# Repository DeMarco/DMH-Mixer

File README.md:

# DMH-Mixer
Simple OpAmp based Mixer module

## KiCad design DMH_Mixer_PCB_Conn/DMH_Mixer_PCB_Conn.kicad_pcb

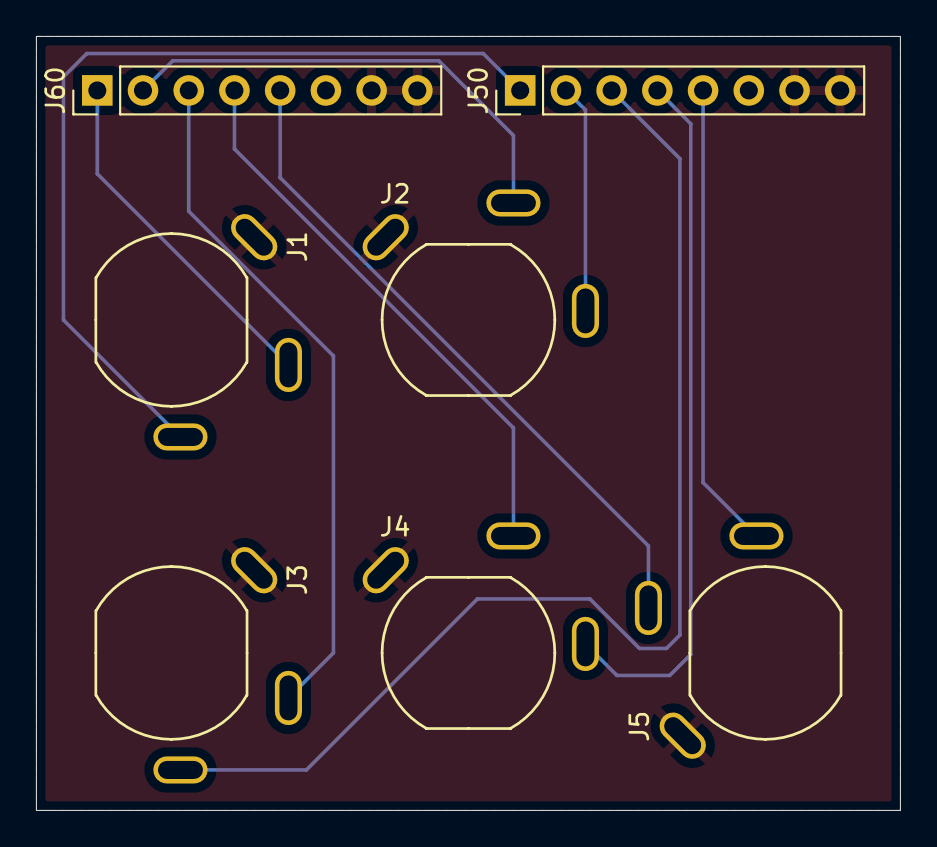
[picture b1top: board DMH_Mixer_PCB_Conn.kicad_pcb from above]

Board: 2 copper layers, 48.0 x 43.0 mm, 7 parts (0 on the bottom side), 11 nets.

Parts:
J1, J2, J3, J4, J5: TS_Jack_6.35mm_Sw; CUI_MJ-63052A
J50, J60: Conn_01x08; PinHeader_1x08_P2.54mm_Vertical

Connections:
/Inputs and Outputs/Input 1 Jack: J1.T, J50.1
/Inputs and Outputs/Input 2 Jack: J2.T, J50.2
/Inputs and Outputs/Input 3 Jack: J3.T, J50.3
/Inputs and Outputs/Input 4 Jack: J4.T, J50.4
/Inputs and Outputs/Output Jack: J5.T, J50.5
GND: J1.S, J2.S, J3.S, J4.S, J5.S, J50.7, J50.8, J60.7, J60.8
unnamed: J1.TN, J60.1
unnamed: J2.TN, J60.2
unnamed: J3.TN, J60.3
unnamed: J4.TN, J60.4
unnamed: J5.TN, J60.5

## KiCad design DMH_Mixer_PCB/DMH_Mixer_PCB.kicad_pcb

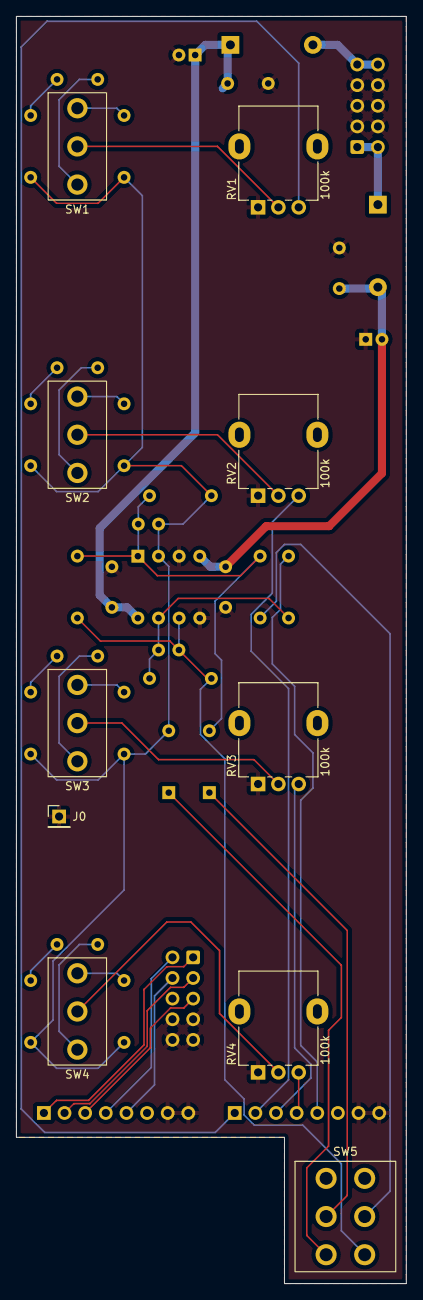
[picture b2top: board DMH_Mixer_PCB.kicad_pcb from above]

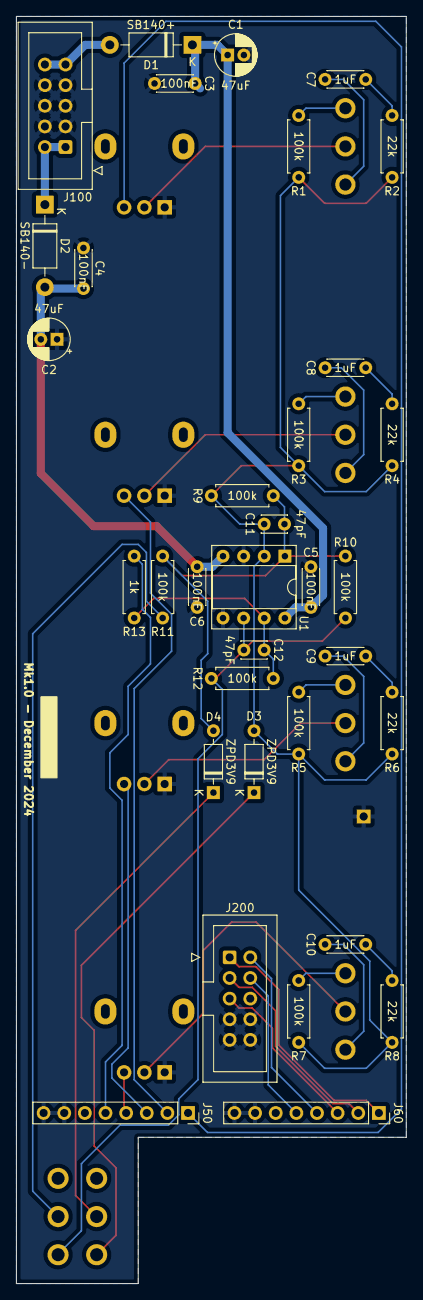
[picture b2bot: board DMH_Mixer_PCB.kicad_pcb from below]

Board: 2 copper layers, 48.0 x 156.0 mm, 44 parts (34 on the bottom side), 38 nets.

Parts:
C1, C2: 47uF; CP_Radial_D5.0mm_P2.00mm
C3, C4, C5, C6: 100nF; C_Disc_D4.3mm_W1.9mm_P5.00mm
C7, C8, C9, C10: 1uF; C_Disc_D4.3mm_W1.9mm_P5.00mm
C11, C12: 47pF; C_Disc_D3.0mm_W2.0mm_P2.50mm
D1: SB140+; D_DO-41_SOD81_P10.16mm_Horizontal
D2: SB140-; D_DO-41_SOD81_P10.16mm_Horizontal
D3, D4: ZPD3V9; D_DO-35_SOD27_P7.62mm_Horizontal
J0: Conn_01x01; PinHeader_1x01_P2.54mm_Vertical
J50, J60: Conn_01x08; PinSocket_1x08_P2.54mm_Vertical
J100: IDC_02x05; IDC-Header_2x05_P2.54mm_Vertical_Eurorack
J200: IDC_02x05; IDC-Header_2x05_P2.54mm_Vertical_BackBone
R1, R3, R5, R7, R9, R10, R11, R12: 100k; R_Axial_DIN0207_L6.3mm_D2.5mm_P7.62mm_Horizontal
R2, R4, R6, R8: 22k; R_Axial_DIN0207_L6.3mm_D2.5mm_P7.62mm_Horizontal
R13: 1k; R_Axial_DIN0207_L6.3mm_D2.5mm_P7.62mm_Horizontal
RV1, RV2, RV3, RV4: 100k; Potentiometer_Alpha_RD901F-40-00D_Single_Vertical
SW1, SW2, SW3, SW4: SW_SPDT_321; Toggle_Switch_THT
SW5: SW_DPDT; Toggle_Switch_2_Poles_THT
U1: TL072; DIP-8_W7.62mm_Socket

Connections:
+12V: C1.1, C3.1, C5.1, D1.1 (K), U1.8 (V+)
-12V: C2.2, C4.2, C6.2, D2.2 (A), U1.4 (V-)
/Core Circuit/Input 1: J50.1, RV1.3
/Core Circuit/Input 2: J50.2, RV2.3
/Core Circuit/Input 3: J50.3, RV3.3
/Core Circuit/Input 4: J50.4, RV4.3
/Core Circuit/Output: J50.5, R13.2
GND: C1.2, C2.1, C3.2, C4.1, C5.2, C6.1, J0.1, J50.7, J50.8, J60.7, J60.8, J100.2a, J100.2b, J100.3a, J100.3b, J100.4a, J100.4b, J200.4, J200.5, J200.9, J200.10, RV1.1, RV2.1, RV3.1, RV4.1, U1.3 (+), U1.5 (+)
unnamed: C7.2, R2.1
unnamed: C8.2, R4.1
unnamed: C9.2, R6.1
unnamed: C10.2, R8.1
unnamed: C12.2, R12.2, R13.1, U1.7
unnamed: D1.2 (A), J100.5a, J100.5b
unnamed: D2.1 (K), J100.1a, J100.1b
unnamed: C11.1, D3.2 (A), R1.2, R2.2, R3.2, R4.2, R5.2, R6.2, R7.2, R8.2, R9.1, U1.2 (-)
unnamed: D3.1 (K), SW5.1 (A)
unnamed: C11.2, D4.2 (A), R9.2, R10.1, R11.2, U1.1
unnamed: D4.1 (K), SW5.2 (B)
unnamed: J60.1, J200.1
unnamed: J60.2, J200.2
unnamed: J60.3, J200.3
unnamed: J60.4, J200.6
unnamed: J60.5, J200.7
unnamed: R11.1, SW5.5 (B)
unnamed: R1.1, SW1.3 (A)
unnamed: RV1.2, SW1.2 (B)
unnamed: C7.1, SW1.1 (C)
unnamed: R3.1, SW2.3 (A)
unnamed: RV2.2, SW2.2 (B)
unnamed: C8.1, SW2.1 (C)
unnamed: R5.1, SW3.3 (A)
unnamed: RV3.2, SW3.2 (B)
unnamed: C9.1, SW3.1 (C)
unnamed: R7.1, SW4.3 (A)
unnamed: RV4.2, SW4.2 (B)
unnamed: C10.1, SW4.1 (C)
unnamed: C12.1, R10.2, R12.1, SW5.4 (A), U1.6 (-)

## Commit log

2024-09-18 Created PANEL KiCad project
2024-09-18 Created PCB KiCad project
2024-09-18 Designed mixer front panel
2024-09-18 Moved clipping knob to the right
2024-09-19 PCB work in progress
2024-09-20 Component placing in progress
2024-09-20 Finished main PCB
2024-09-20 Finished connectors PCB
2024-09-20 Added SynthStuff as submodule
2024-09-22 Synced 3D models and drawing layers
2024-09-22 Sync libs
2024-09-23 Updated fps with their 3D models
2024-09-23 Breadboarding ongoing
2024-09-24 Replaced clipping with 4th channel on panel
2024-09-24 Added 4th channel to schematic
    ... and replaced Inverted Output with Clipped Output
2024-09-24 PCB redesign in progress
2024-09-24 Rerouted main PCB
2024-10-03 Adapted connectors PCB to 4 channel
2024-10-17 Added toggle switches to front panel
2024-10-17 Added switches to schematic
2024-10-17 Component placement ongoing
2024-10-18 Moved pots to X=83,25
2024-10-18 Added AC coupling
2024-10-18 Component placement done
2024-10-18 ReRouted PCB
2024-10-20 Moved output jacks to bottom right
2024-10-22 Added Zener limiting
2024-10-26 Update Core_Circuit.kicad_sch
    Added 47pF to last opamp stage
    Changed zeners to 3V9
    Changed additional gain resistor to 100k
2024-10-27 Output selection in progress
2024-10-27 Finalization in progress
2024-10-27 Finalized schematic
2024-10-28 PCB redesign ongoing
2024-10-29 PCB Component placement ready
2024-10-29 Finished routing main PCB
2024-10-29 Panel and Connectors PCB ready
2024-12-03 Prepared Gerbers for production
2024-12-04 Changed module name to AC & DC in panel
2024-12-08 Generated BoM
2026-05-01 Created 6 channel panel version
